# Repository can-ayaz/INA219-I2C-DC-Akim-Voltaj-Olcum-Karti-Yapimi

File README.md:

# INA219-I2C-DC-Akim-Voltaj-Olcum-Karti-Yapimi
**INA219 I²C DC Akım-Voltaj Ölçüm Kartı Yapımı**

Merhaba, Bu yazımızda bir IoT projemde güç tüketimini hesaplamak ihtiyacı duydum ve projeme en uygun olan Texas Instruments üretimi olan INA219 entegresini kullnarak bir PCB tasarladıktan sonra akım ve voltaj ölçüp I²C  protoklü üzerinden  %1 hassasiyetle ölçeceğiz.

**Daha fazlası içi ziyaret edebilirsiniz: https://canayazblog.wordpress.com/**

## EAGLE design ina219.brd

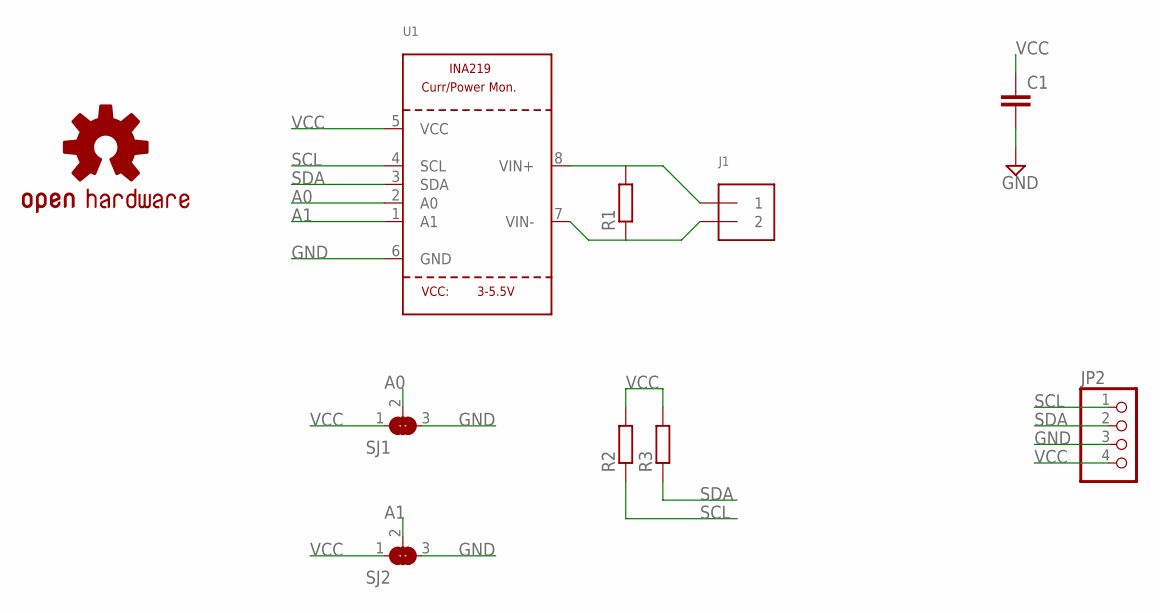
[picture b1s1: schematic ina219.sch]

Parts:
C1: C-EUC0805; C0805
J1: TERMBLOCK_1X2; TERMBLOCK_1X2-3.5MM
JP2: PINHD-1X4; 1X04
LOGO1: OSHW-LOGOS; OSHW-LOGO-S
R1: R-EU_R1206; R1206
R2, R3: R-EU_R0805; R0805
SJ1, SJ2: SOLDERJUMPER_2WAY0603; SOLDERJUMPER_2WAY_OPEN_0603
U1: INA219SOIC8; SOIC8_150MIL

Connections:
A0: SJ1.2, U1.2 (A0)
A1: SJ2.2, U1.1 (A1)
GND: C1.2, JP2.3, SJ1.3, SJ2.3, U1.6 (GND)
unnamed: J1.1, R1.2, U1.8 (VIN+)
unnamed: J1.2, R1.1, U1.7 (VIN-)
SCL: JP2.1, R2.1, U1.4 (SCL)
SDA: JP2.2, R3.1, U1.3 (SDA)
VCC: C1.1, JP2.4, R2.2, R3.2, SJ1.1, SJ2.1, U1.5 (VCC)

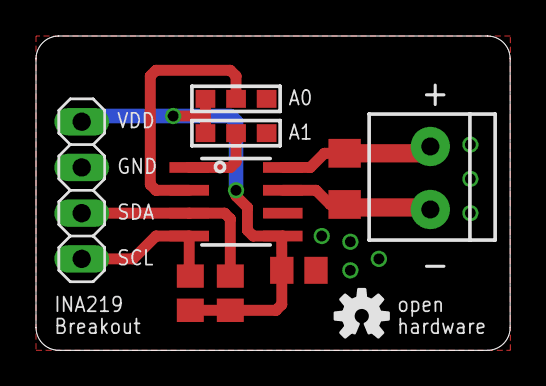
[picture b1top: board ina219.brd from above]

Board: 2 copper layers, 26.3 x 17.5 mm, 10 parts (0 on the bottom side), 8 nets.

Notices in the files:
parts and their libraries:
microbuilder: This work is placed in the public domain, and may be freely used for commercial and non-commercial work with the following conditions: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
SparkFun-Aesthetics: Licensing: CC v3.0 Share-Alike You are welcome to use this library for commercial purposes.
